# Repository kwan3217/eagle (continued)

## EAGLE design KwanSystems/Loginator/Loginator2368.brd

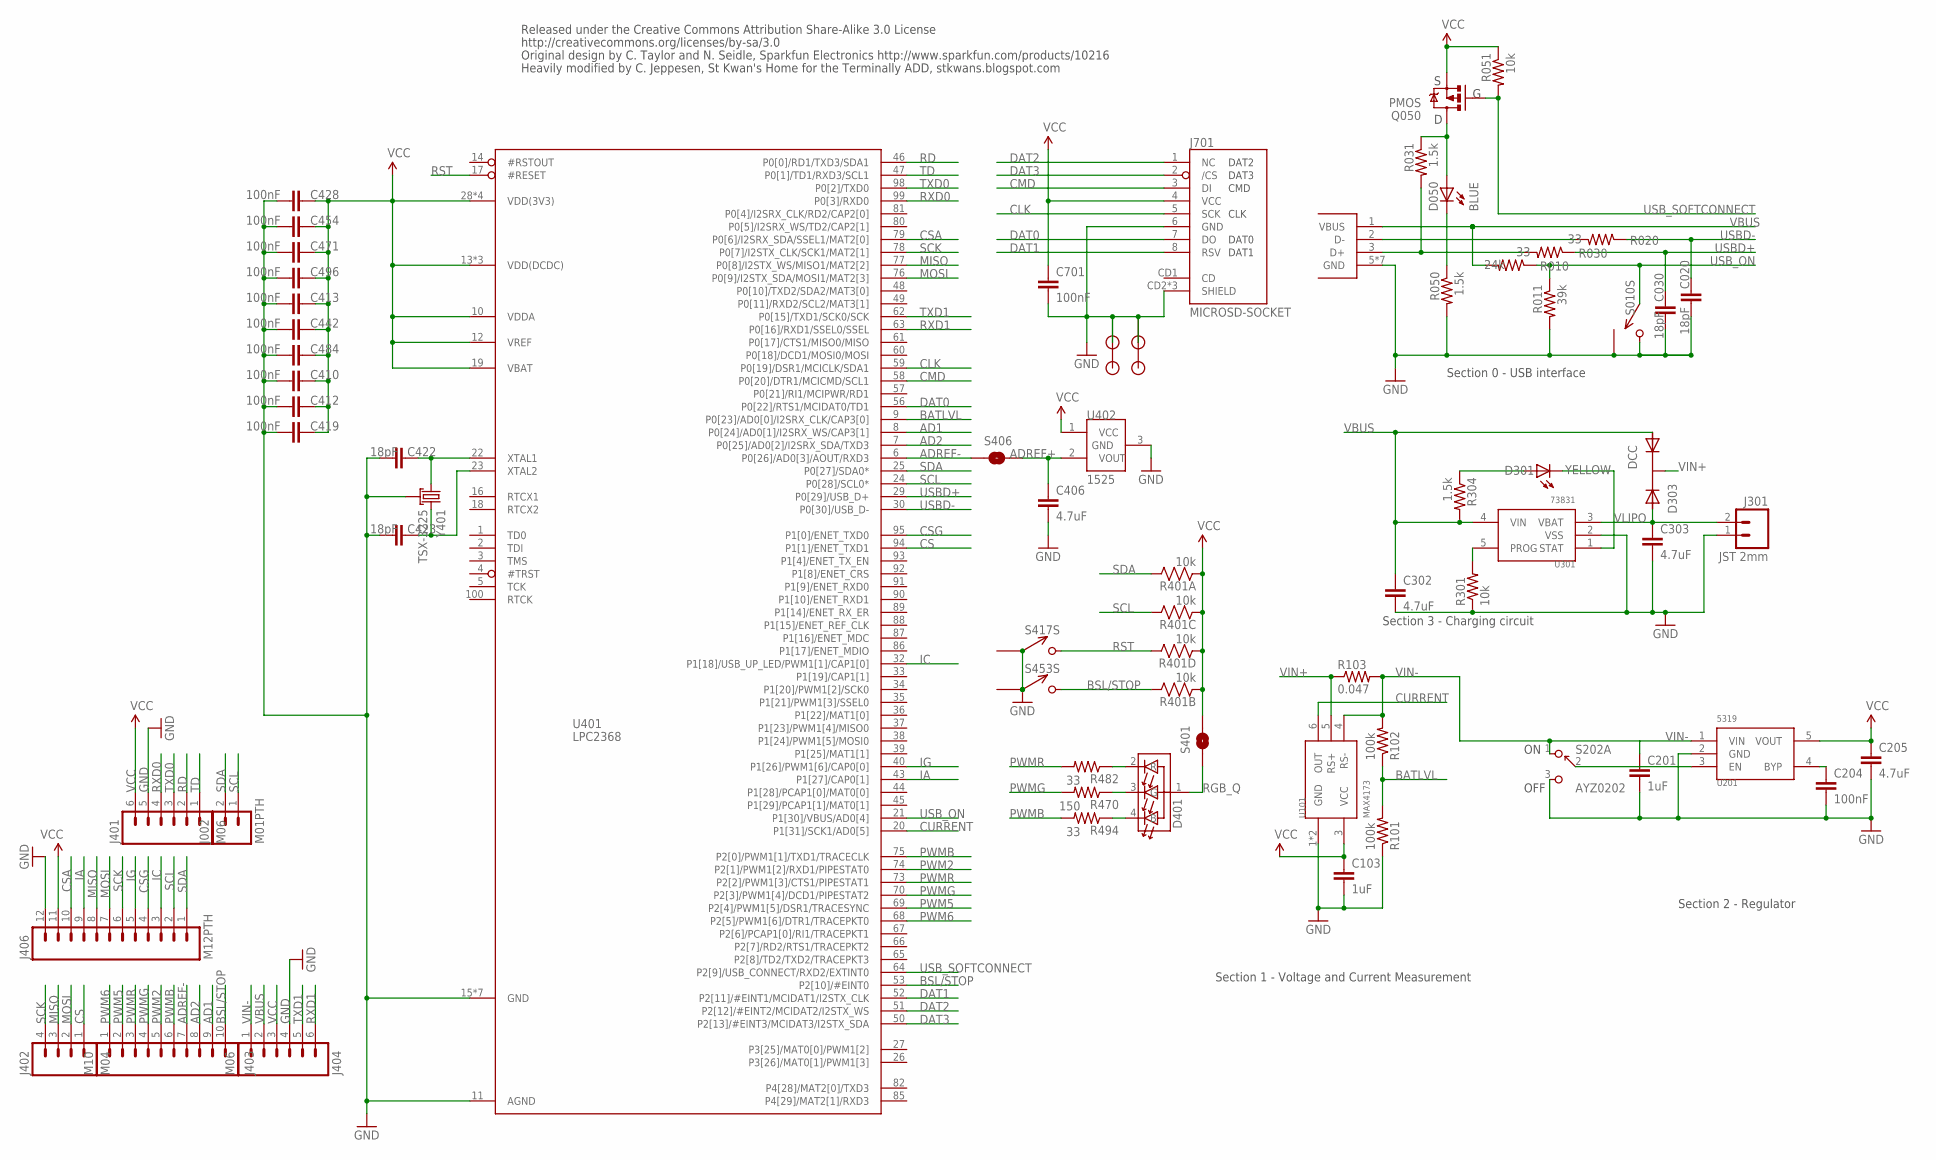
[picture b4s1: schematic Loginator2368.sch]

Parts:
C020, C030, C422, C423: 18pF; 0402-CAP; DIGIKEY 445-1238-1-ND
C103, C201: 1uF; 0402-CAP; DIGIKEY 445-1415-1-ND
C204, C410, C412, C413, C419, C428, C442, C454, C471, C484, C496, C701: 100nF; 0402-CAP; DIGIKEY 445-1268-1-ND
C205, C302, C303, C406: 4.7uF; 0402-CAP; DIGIKEY 445-7395-1-ND
D050: BLUE; LED-0603; DIGIKEY 754-1434-1-ND
D301: YELLOW; LED-0603; DIGIKEY 754-1354-1-ND
D303: DCC; SOT-23-3; DIGIKEY 568-6500-1-ND
D401: RGB; HSMF-C118; DIGIKEY 516-1778-1-ND
J001: USB_MICROB_JSTFCI; USB-MICROB-CONN-09505; DIGIKEY 670-1190-1-ND
J002: M01PTH; 1X02; DIGIKEY $NOPART
J301: JST 2mm; JST-2-SMD; DIGIKEY 455-1749-1-ND
J401, J404: M06; 1X06; DIGIKEY $NOPART
J402: M04; 1X04; DIGIKEY $NOPART
J403: M10; 1X10; DIGIKEY $NOPART
J406: M12PTH; 1X12; DIGIKEY $NOPART
J701: MICROSD-SOCKET; MICROSD-SOCKET-PP; DIGIKEY 101-00581-59-1-ND
JP1, JP2, JP3, JP4: STANDOFF; DIGIKEY $NOPART
Q050: PMOS; SOT23-3; DIGIKEY NTR1P02T1GOSCT-ND
R010: 24k; 0402-RES; DIGIKEY P10.0KLCT-ND
R011: 39k; 0402-RES; DIGIKEY P100KLCT-ND
R020, R030, R482, R494: 33; 0402-RES; DIGIKEY P33.0LCT-ND
R031, R050, R304: 1.5k; 0402-RES; DIGIKEY P1.50KLCT-ND
R051, R301: 10k; 0402-RES; DIGIKEY P10.0KLCT-ND
R101, R102: 100k; 0402-RES; DIGIKEY P100KLCT-ND
R103: 0.047; 0402-RES; DIGIKEY P.047ATCT-ND
R401: 10k; CRA04; DIGIKEY CRA4S810KCT-ND
R470: 150; 0402-RES; DIGIKEY P150LCT-ND
S010, S417, S453: SPST; B3U-1100P; DIGIKEY SW1021CT-ND
S202: AYZ0202
S401, S406: SOLDERJUMPERNO; SJ_2S-NO; DIGIKEY $NOPART
U101: MAX4173; SOT-23-6
U201: 5319; SOT-23-5; DIGIKEY 576-1910-1-ND
U301: 73831; SOT-23-5; DIGIKEY MCP73831T-2ACI/OTCT-ND
U401: LPC2368; LQFP100; DIGIKEY 568-3997-ND
U402: 1525; SOT-23-3; DIGIKEY MCP1525T-I/TTCT-ND
Y401: TSX-3225; CRYSTAL_SMD

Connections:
AD1: J403.9, U401.8 (P0[24]/AD0[1]/I2SRX_WS/CAP3[1])
AD2: J403.8, U401.7 (P0[25]/AD0[2]/I2SRX_SDA/TXD3)
ADREF+: C406.1, S406.1, U402.2 (VOUT)
ADREF-: J403.7, S406.2, U401.6 (P0[26]/AD0[3]/AOUT/RXD3)
BATLVL: R101.2, R102.1, U401.9 (P0[23]/AD0[0]/I2SRX_CLK/CAP3[0])
BSL/STOP: J403.10, R401.7 (2), S453.P$2 (2), U401.53 (P2[10]/#EINT0)
CLK: J701.5 (SCK), U401.59 (P0[19]/DSR1/MCICLK/SDA1)
CMD: J701.3 (DI), U401.58 (P0[20]/DTR1/MCICMD/SCL1)
CONN_D+: J001.3 (D+), R030.2, R031.2
CONN_D-: J001.2 (D-), R020.2
CS: J402.1, U401.94 (P1[1]/ENET_TXD1)
CSA: J406.10, U401.79 (P0[6]/I2SRX_SDA/SSEL1/MAT2[0])
CSG: J406.4, U401.95 (P1[0]/ENET_TXD0)
CURRENT: U101.6 (OUT), U401.20 (P1[31]/SCK1/AD0[5])
DAT0: J701.7 (DO), U401.56 (P0[22]/RTS1/MCIDAT0/TD1)
DAT1: J701.8 (RSV), U401.52 (P2[11]/#EINT1/MCIDAT1/I2STX_CLK)
DAT2: J701.1 (NC), U401.51 (P2[12]/#EINT2/MCIDAT2/I2STX_WS)
DAT3: J701.2 (/CS), U401.50 (P2[13]/#EINT3/MCIDAT3/I2STX_SDA)
DB: D401.4 (B), R494.1
DG: D401.2 (R), R482.1
DR: D401.3 (G), R470.1
EN: S202.2, U201.3 (EN)
GND: C020.2, C030.2, C103.2, C201.2, C204.2, C205.2, C302.2, C303.2, C406.2, C410.2, C412.2, C413.2, C419.2, C422.1, C423.1, C428.2, C442.2, C454.2, C471.2, C484.2, C496.2, C701.2, J001.5 (GND), J001.P1 (GND), J001.P2 (GND), J001.P3 (GND), J001.P4 (GND), J001.P5 (GND), J001.P6 (GND), J301.1, J401.5, J404.4, J406.12, J701.6 (GND), J701.CD2 (SHIELD), J701.GND1 (SHIELD), J701.GND3 (SHIELD), JP1.P$1, JP2.P$1, JP3.P$1, JP4.P$1, R011.2, R050.2, R101.1, R301.1, S010.P$2 (2), S010.P$3 (1), S202.3, S417.P$1 (1), S417.P$3 (1), S453.P$1 (1), S453.P$3 (1), U101.1 (GND), U101.2 (GND), U201.2 (GND), U301.2 (VSS), U401.11 (AGND), U401.15 (GND), U401.31 (GND), U401.41 (GND), U401.55 (GND), U401.72 (GND), U401.83 (GND), U401.97 (GND), U402.3 (GND), Y401.2 (GND), Y401.4 (GND)
IA: J406.9, U401.43 (P1[27]/CAP0[1])
IC: J406.3, U401.32 (P1[18]/USB_UP_LED/PWM1[1]/CAP1[0])
IG: J406.5, U401.40 (P1[26]/PWM1[6]/CAP0[0])
MISO: J402.3, J406.8, U401.77 (P0[8]/I2STX_WS/MISO1/MAT2[2])
MOSI: J402.2, J406.7, U401.76 (P0[9]/I2STX_SDA/MOSI1/MAT2[3])
unnamed: D301.A, R304.1
unnamed: R301.2, U301.5 (PROG)
unnamed: D301.C, U301.1 (STAT)
unnamed: D050.A, Q050.3 (D), R031.1
unnamed: D050.C, R050.1
unnamed: C204.1, U201.4 (BYP)
PWM2: J403.5, U401.74 (P2[1]/PWM1[2]/RXD1/PIPESTAT0)
PWM5: J403.2, U401.69 (P2[4]/PWM1[5]/DSR1/TRACESYNC)
PWM6: J403.1, U401.68 (P2[5]/PWM1[6]/DTR1/TRACEPKT0)
PWMB: J403.6, R494.2, U401.75 (P2[0]/PWM1[1]/TXD1/TRACECLK)
PWMG: J403.4, R470.2, U401.70 (P2[3]/PWM1[4]/DCD1/PIPESTAT2)
PWMR: J403.3, R482.2, U401.73 (P2[2]/PWM1[3]/CTS1/PIPESTAT1)
RD: J401.2, U401.46 (P0[0]/RD1/TXD3/SDA1)
RGB_Q: D401.1 (A), S401.1
RST: R401.5 (2), S417.P$2 (2), U401.17 (#RESET)
RXD0: J401.4, U401.99 (P0[3]/RXD0)
RXD1: J404.6, U401.63 (P0[16]/RXD1/SSEL0/SSEL)
SCK: J402.4, J406.6, U401.78 (P0[7]/I2STX_CLK/SCK1/MAT2[1])
SCL: J002.1, J406.2, R401.6 (2), U401.24 (P0[28]/SCL0*)
SDA: J002.2, J406.1, R401.8 (2), U401.25 (P0[27]/SDA0*)
TD: J401.1, U401.47 (P0[1]/TD1/RXD3/SCL1)
TXD0: J401.3, U401.98 (P0[2]/TXD0)
TXD1: J404.5, U401.62 (P0[15]/TXD1/SCK0/SCK)
USBD+: C030.1, R030.1, U401.29 (P0[29]/USB_D+)
USBD-: C020.1, R020.1, U401.30 (P0[30]/USB_D-)
USB_ON: R010.1, R011.1, S010.P$1 (1), U401.21 (P1[30]/VBUS/AD0[4])
USB_SOFTCONNECT: Q050.1 (G), R051.2, U401.64 (P2[9]/USB_CONNECT/RXD2/EXTINT0)
VBUS: C302.1, D303.1 (A1), J001.1 (VBUS), J404.2, R010.2, R304.2, U301.4 (VIN)
VCC: C103.1, C205.1, C410.1, C412.1, C413.1, C419.1, C428.1, C442.1, C454.1, C471.1, C484.1, C496.1, C701.1, J401.6, J404.3, J406.11, J701.4 (VCC), Q050.2 (S), R051.1, R401.1, R401.2 (1), R401.3 (1), R401.4 (1), S401.2, U101.3 (VCC), U201.5 (VOUT), U401.10 (VDDA), U401.12 (VREF), U401.13 (VDD(DCDC)), U401.19 (VBAT), U401.28 (VDD(3V3)), U401.42 (VDD(DCDC)), U401.54 (VDD(3V3)), U401.71 (VDD(3V3)), U401.84 (VDD(DCDC)), U401.96 (VDD(3V3)), U402.1 (VCC)
VIN+: D303.3 (K), R103.1, U101.5 (RS+)
VIN-: C201.1, J404.1, R102.2, R103.2, S202.1, U101.4 (RS-), U201.1 (VIN)
VLIPO: C303.1, D303.2 (A2), J301.2, U301.3 (VBAT)
XTAL1: C422.2, U401.22 (XTAL1), Y401.1
XTAL2: C423.2, U401.23 (XTAL2), Y401.3 (2)

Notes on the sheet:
Section 2 - Regulator
Section 3 - Charging circuit
Section 0 - USB interface
Released under the Creative Commons Attribution Share-Alike 3.0 License
http://creativecommons.org/licenses/by-sa/3.0
Original design by C. Taylor and N. Seidle, Sparkfun Electronics http://www.sparkfun.com/products/10216
Heavily modified by C. Jeppesen, St Kwan's Home for the Terminally ADD, stkwans.blogspot.com
Section 1 - Voltage and Current Measurement
OFF

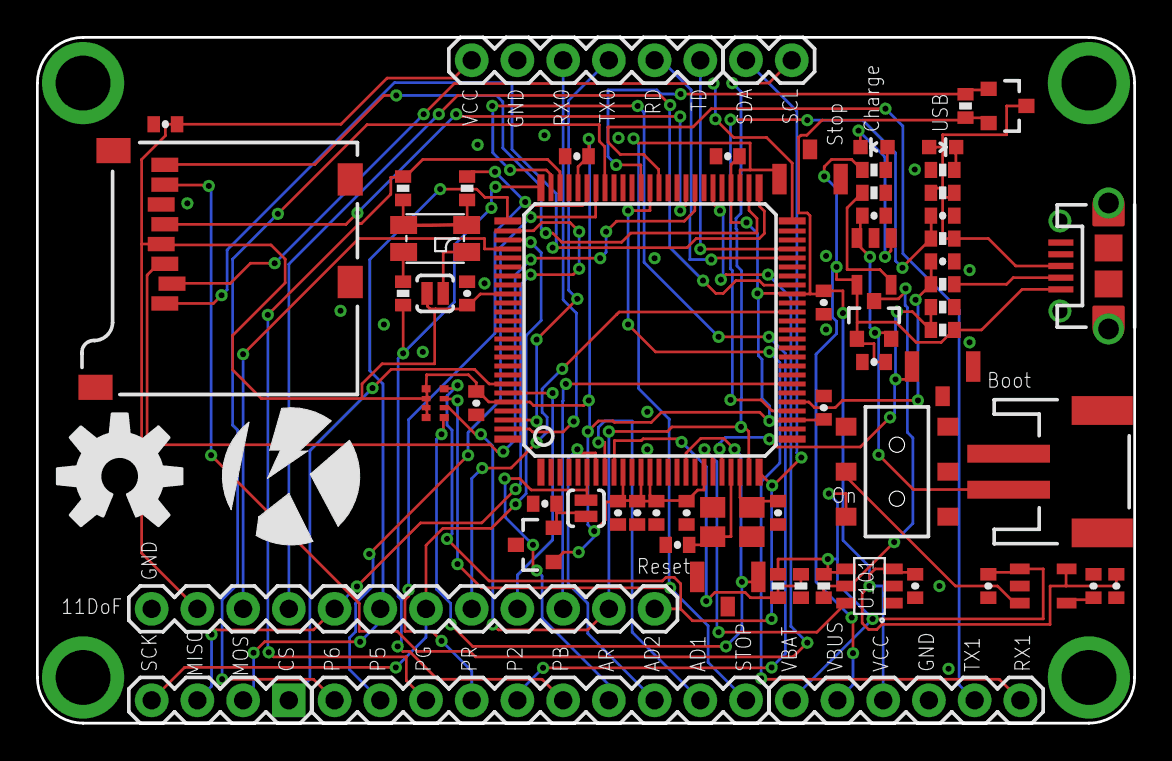
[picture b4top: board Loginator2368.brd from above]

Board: 2 copper layers, 61.0 x 38.1 mm, 70 parts (0 on the bottom side), 62 nets.

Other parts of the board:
U$1: KWAN_CIRCLE
U$2: OSHW-LOGO-L

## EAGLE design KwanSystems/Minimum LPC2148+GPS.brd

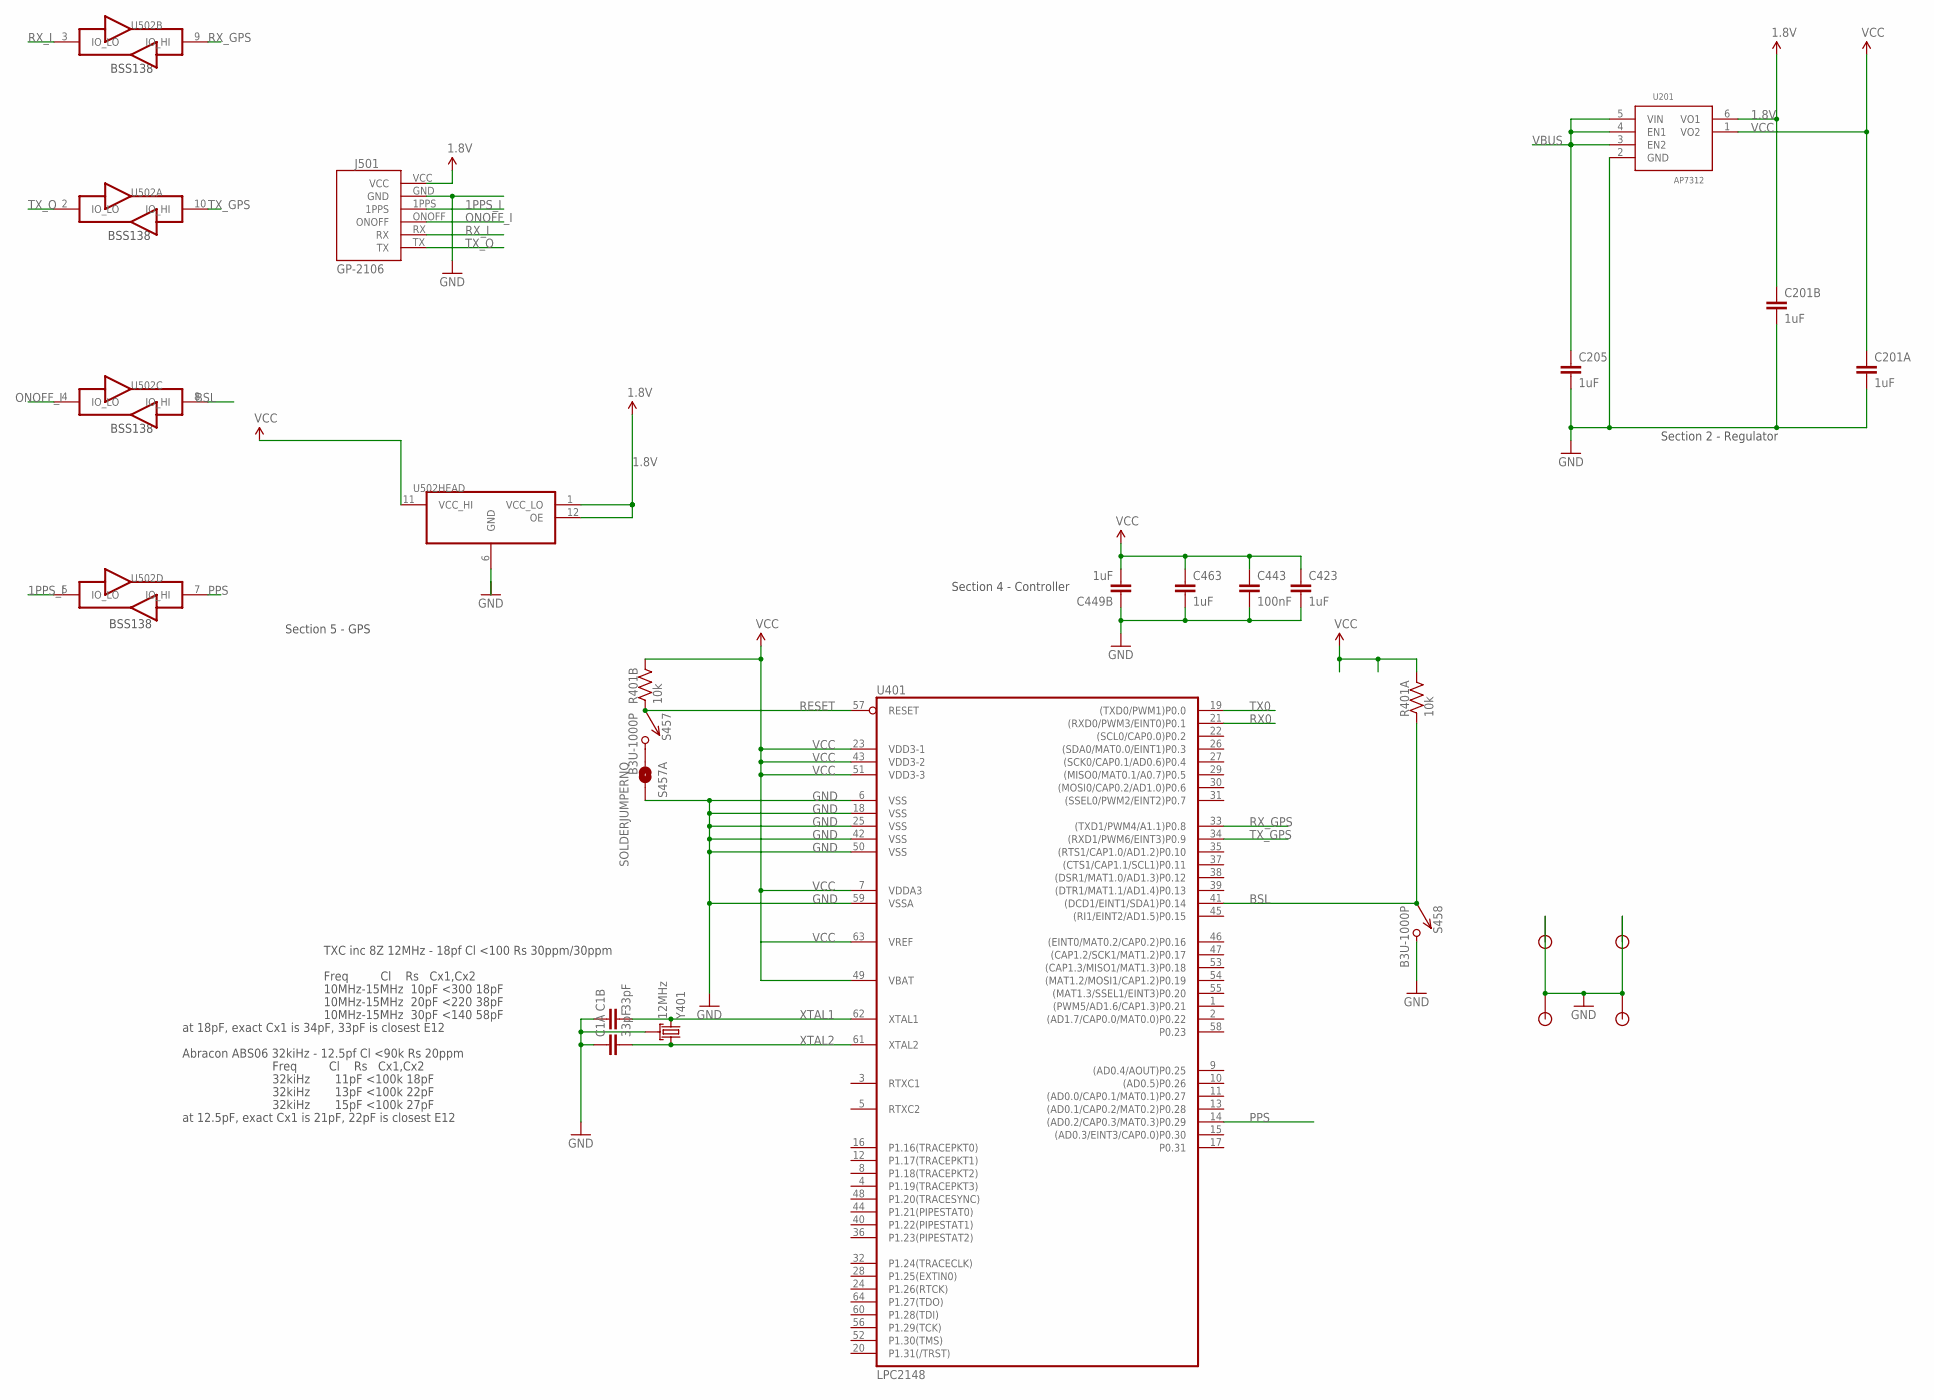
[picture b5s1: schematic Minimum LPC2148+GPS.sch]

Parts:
C1: 33pF; CKCM25
C201, C449: 1uF; CKCM25
C205, C423, C463: 1uF; 0402-CAP; DIGIKEY 445-4114-1-ND
C443: 100nF; 0402-CAP; DIGIKEY 445-1265-1-ND
J501: GP-2106
JP1, JP2, JP4, JP5: STANDOFF; DIGIKEY $NOPART
R401: 10k; CRA02; DIGIKEY CRA4S810KCT-ND
S457, S458: B3U-1000P; DIGIKEY SW1020CT-ND
S457A: SOLDERJUMPERNO; SJ_2S-NO; DIGIKEY $NOPART
U201: AP7312; SOT-23-6
U401: LPC2148; SQFP-S-10X10-64; DIGIKEY 568-1765-ND
U502: TXB0104RUT; R-PUQFN-N12
Y401: 12MHz; CRYSTAL_SMD_2MM_2_5MM; DIGIKEY 887-1487-1-ND

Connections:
1.8V: C201.2 (1), J501.VCC, U201.6 (VO1), U502.1 (VCC_LO), U502.12 (OE)
1PPS_I: J501.1PPS, U502.5 (IO_LO)
BSL: R401.1, S458.P$1 (1), U401.41 ((DCD1/EINT1/SDA1)P0.14), U502.8 (IO_HI)
GND: C1.1, C1.2 (1), C201.3 (2), C201.4 (2), C205.2, C423.2, C443.2, C449.2 (1), C463.2, J501.GND, JP1.P$1, JP2.P$1, JP4.P$1, JP5.P$1, S457A.2, S458.P$2 (2), U201.2 (GND), U401.6 (VSS), U401.18 (VSS), U401.25 (VSS), U401.42 (VSS), U401.50 (VSS), U401.59 (VSSA), U502.6 (GND), Y401.2 (GND), Y401.4 (GND)
unnamed: S457.P$2 (2), S457A.1
ONOFF_I: J501.ONOFF, U502.4 (IO_LO)
PPS: U401.14 ((AD0.2/CAP0.3/MAT0.3)P0.29), U502.7 (IO_HI)
RESET: R401.2 (1), S457.P$1 (1), U401.57 (RESET)
RX0: U401.21 ((RXD0/PWM3/EINT0)P0.1)
RX_GPS: U401.33 ((TXD1/PWM4/A1.1)P0.8), U502.9 (IO_HI)
RX_I: J501.RX, U502.3 (IO_LO)
TX0: U401.19 ((TXD0/PWM1)P0.0)
TX_GPS: U401.34 ((RXD1/PWM6/EINT3)P0.9), U502.10 (IO_HI)
TX_O: J501.TX, U502.2 (IO_LO)
VBUS: C205.1, U201.3 (EN2), U201.4 (EN1), U201.5 (VIN)
VCC: C201.1, C423.1, C443.1, C449.3 (2), C463.1, R401.3 (2), R401.4 (2), U201.1 (VO2), U401.7 (VDDA3), U401.23 (VDD3-1), U401.43 (VDD3-2), U401.49 (VBAT), U401.51 (VDD3-3), U401.63 (VREF), U502.11 (VCC_HI)
XTAL1: C1.3 (2), U401.62 (XTAL1), Y401.3 (2)
XTAL2: C1.4 (2), U401.61 (XTAL2), Y401.1

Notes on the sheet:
Section 2 - Regulator
Section 4 - Controller
Freq Cl Rs Cx1,Cx2
10MHz-15MHz 10pF <300 18pF
10MHz-15MHz 20pF <220 38pF
10MHz-15MHz 30pF <140 58pF
TXC inc 8Z 12MHz - 18pf Cl <100 Rs 30ppm/30ppm
at 18pF, exact Cx1 is 34pF, 33pF is closest E12
32kiHz 11pF <100k 18pF
32kiHz 13pF <100k 22pF
32kiHz 15pF <100k 27pF
Abracon ABS06 32kiHz - 12.5pf Cl <90k Rs 20ppm
at 12.5pF, exact Cx1 is 21pF, 22pF is closest E12
BSS138
Section 5 - GPS

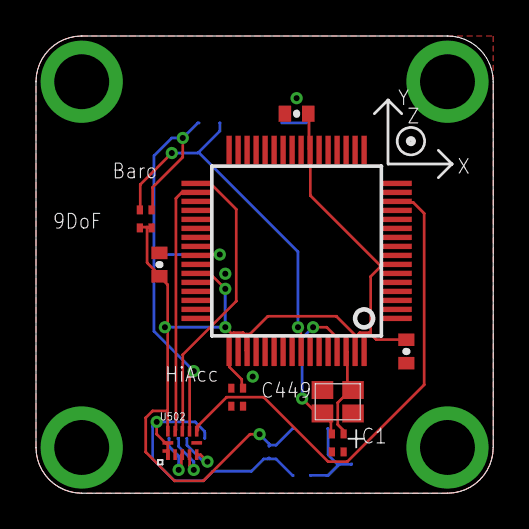
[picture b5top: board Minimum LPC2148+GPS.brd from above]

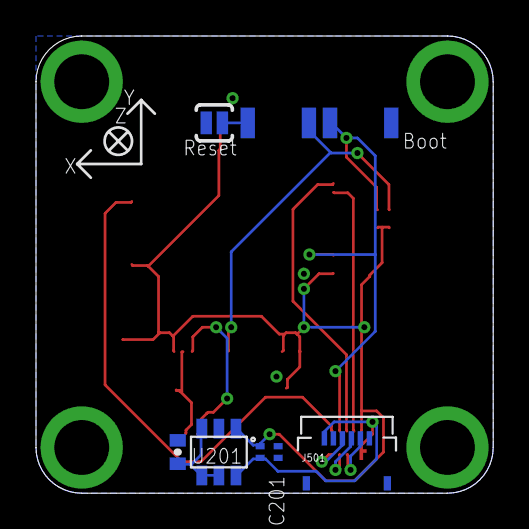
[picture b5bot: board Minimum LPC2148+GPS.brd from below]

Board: 2 copper layers, 25.4 x 25.4 mm, 21 parts (7 on the bottom side), 16 nets.

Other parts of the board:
U$4: AXES
